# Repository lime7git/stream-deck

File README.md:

# stream-deck
 
TO DO:

- ADD RESET BUTTON                                     #CHECK
- CHANGE SWD TO GOLDPINS                               #CHECK
- ADD TWO STATUS LED DIODES                            #CHECK
- ADD FOOTPRINTS FOR MX CHERRY REPLACEMENT SWITCHES    #CHECK
- ADD TEST POINTS                                      #CHECK

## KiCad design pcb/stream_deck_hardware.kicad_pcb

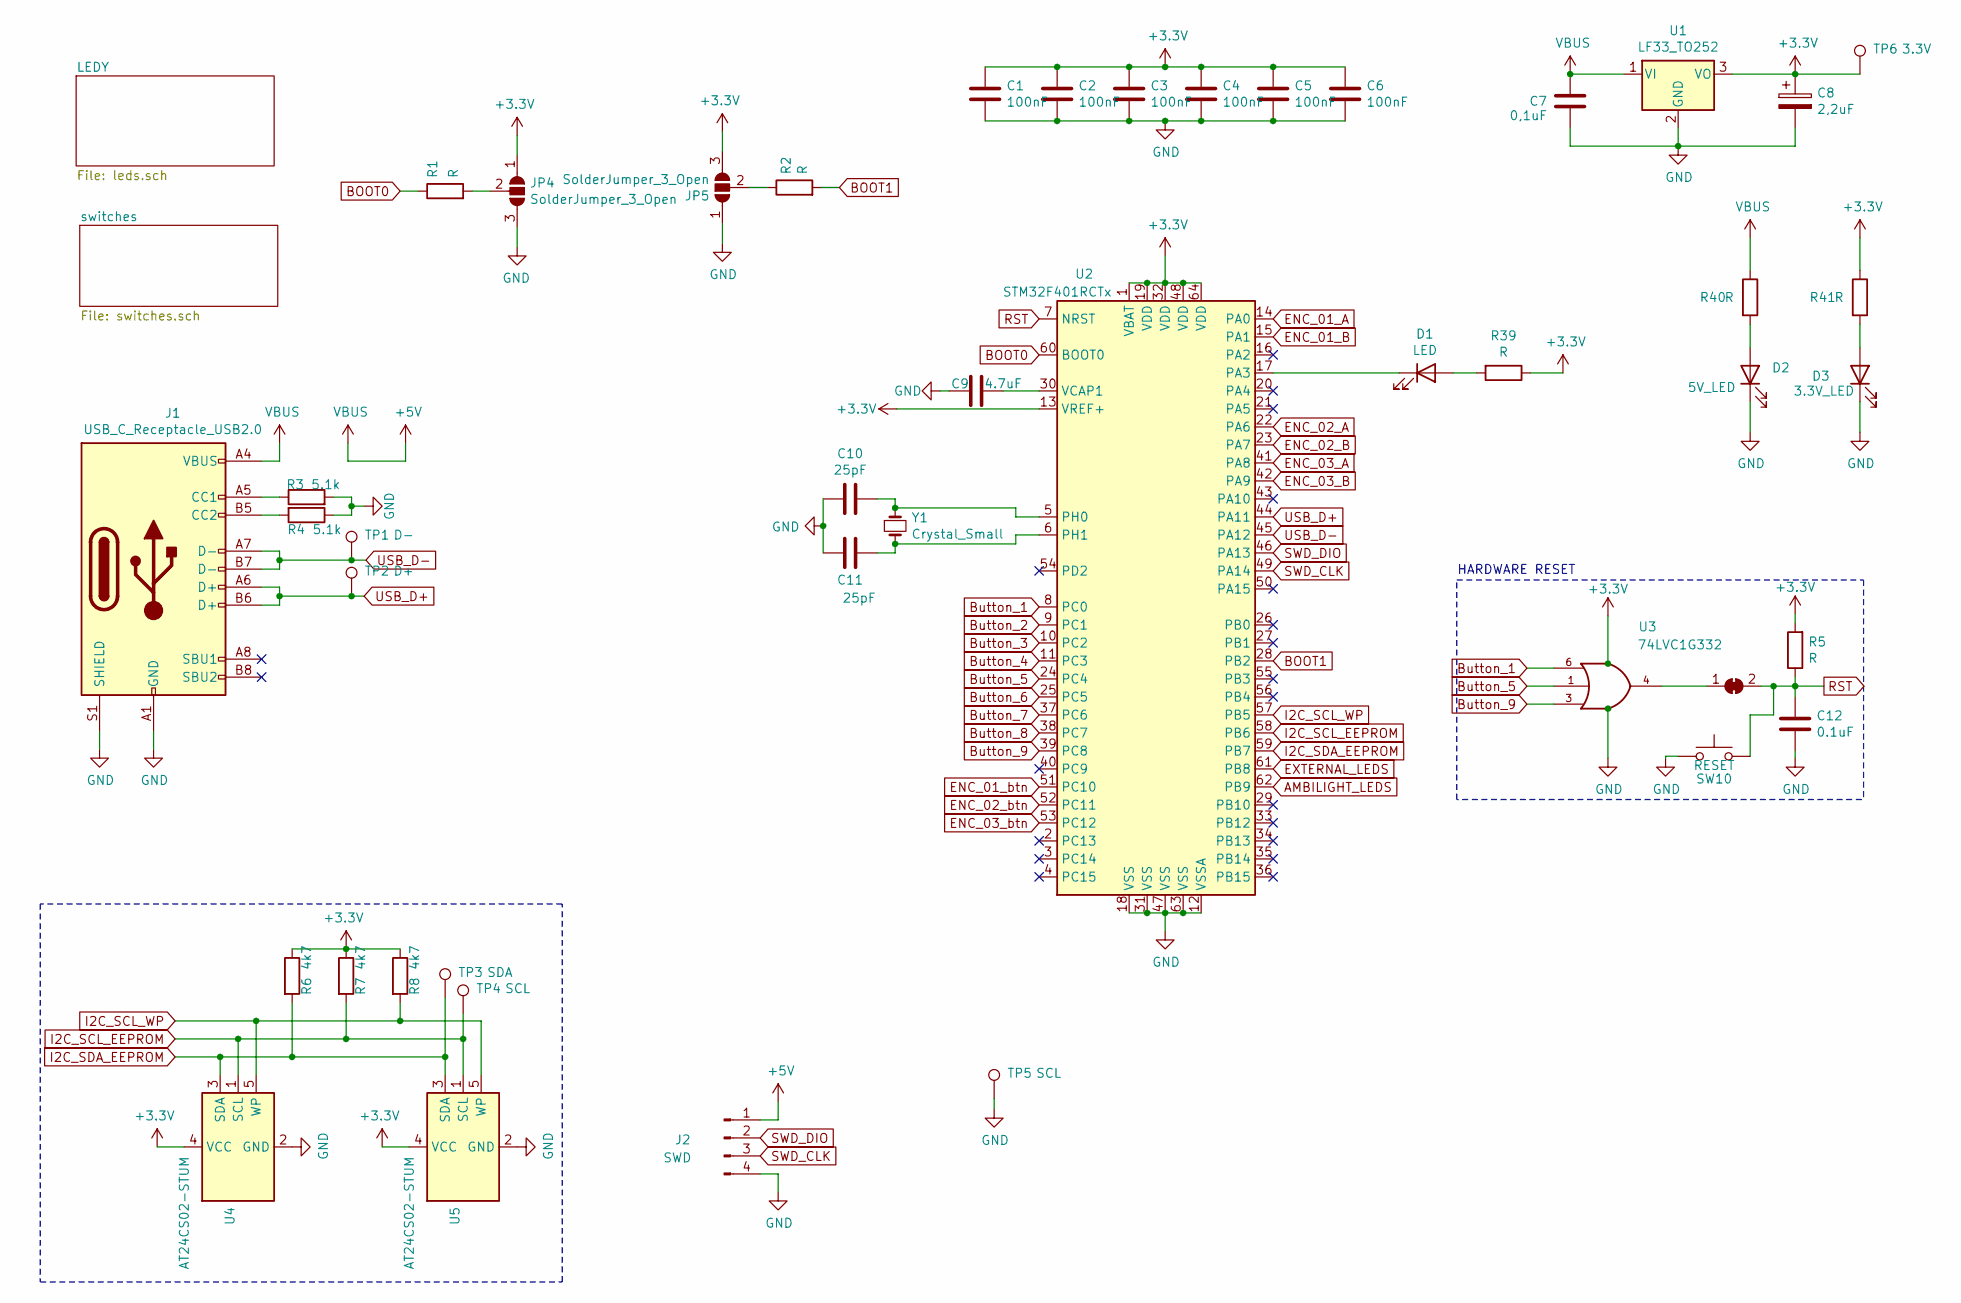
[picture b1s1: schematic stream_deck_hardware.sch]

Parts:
C1, C2, C3, C4, C5, C6: 100nF; C_0603_1608Metric
C7: 0,1uF; C_0603_1608Metric
C8: 2,2uF; C_0603_1608Metric
C9: 4.7uF; C_0603_1608Metric
C10, C11: 25pF; C_0603_1608Metric
C12: 0.1uF; C_0603_1608Metric
D1: LED; LED_0805_2012Metric
D2: 5V_LED; LED_0805_2012Metric
D3: 3.3V_LED; LED_0805_2012Metric
J1: USB_C_Receptacle_USB2.0; USB_C_Receptacle_Palconn_UTC16-G
J2: SWD; PinHeader_1x04_P2.54mm_Vertical
JP3: SolderJumper_2_Bridged; SolderJumper-2_P1.3mm_Bridged2Bar_RoundedPad1.0x1.5mm
JP4, JP5: SolderJumper_3_Open; SolderJumper-3_P1.3mm_Open_RoundedPad1.0x1.5mm
R1, R2, R5, R39, R40, R41: R; R_0603_1608Metric
R3, R4: 5.1k; R_0603_1608Metric
R6, R7, R8: 4k7; R_0603_1608Metric
SW10: RESET; SW_PUSH_6mm
TP1: D-; TestPoint_Pad_D2.0mm
TP2: D+; TestPoint_Pad_D2.0mm
TP3: SDA; TestPoint_Pad_D2.0mm
TP4, TP5: SCL; TestPoint_Pad_D2.0mm
TP6: 3.3V; TestPoint_Pad_D2.0mm
U1: LF33_TO252; TO-252-2
U2: STM32F401RCTx; LQFP-64_10x10mm_P0.5mm
U3: 74LVC1G332; SOT-23-6
U4, U5: AT24CS02-STUM; SOT-23-5
Y1: Crystal_Small; Crystal_HC49-U_Vertical

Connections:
+3V3: C1.1, C2.1, C3.1, C4.1, C5.1, C6.1, C8.1, JP4.1 (A), JP5.3 (B), R5.2, R6.1, R7.1, R8.1, R39.1, R41.1, TP6.1, U1.3 (VO), U2.1 (VBAT), U2.13 (VREF+), U2.19 (VDD), U2.32 (VDD), U2.48 (VDD), U2.64 (VDD), U3.5 (VCC), U4.4 (VCC), U5.4 (VCC); also elsewhere on the board
+5V: C7.1, J1.A4 (VBUS), J1.A9 (VBUS), J1.B4 (VBUS), J1.B9 (VBUS), J2.1, R40.1, U1.1 (VI); also elsewhere on the board
AMBILIGHT_LEDS: U2.62 (PB9); also elsewhere on the board
BOOT0: R1.1, U2.60 (BOOT0)
BOOT1: R2.2, U2.28 (PB2)
Button_1: U2.8 (PC0), U3.6; also elsewhere on the board
Button_2: U2.9 (PC1); also elsewhere on the board
Button_3: U2.10 (PC2); also elsewhere on the board
Button_4: U2.11 (PC3); also elsewhere on the board
Button_5: U2.24 (PC4), U3.1; also elsewhere on the board
Button_6: U2.25 (PC5); also elsewhere on the board
Button_7: U2.37 (PC6); also elsewhere on the board
Button_8: U2.38 (PC7); also elsewhere on the board
Button_9: U2.39 (PC8), U3.3; also elsewhere on the board
ENC_01_A: U2.14 (PA0); also elsewhere on the board
ENC_01_B: U2.15 (PA1); also elsewhere on the board
ENC_01_btn: U2.51 (PC10); also elsewhere on the board
ENC_02_A: U2.22 (PA6); also elsewhere on the board
ENC_02_B: U2.23 (PA7); also elsewhere on the board
ENC_02_btn: U2.52 (PC11); also elsewhere on the board
ENC_03_A: U2.41 (PA8); also elsewhere on the board
ENC_03_B: U2.42 (PA9); also elsewhere on the board
ENC_03_btn: U2.53 (PC12); also elsewhere on the board
EXTERNAL_LEDS: U2.61 (PB8); also elsewhere on the board
GND: C1.2, C2.2, C3.2, C4.2, C5.2, C6.2, C7.2, C8.2, C9.1, C10.2, C11.2, C12.2, D2.1 (K), D3.1 (K), J1.A1 (GND), J1.A12 (GND), J1.B1 (GND), J1.B12 (GND), J1.S1 (SHIELD), J2.4, JP4.3 (B), JP5.1 (A), R3.2, R4.1, SW10.1, TP5.1, U1.2 (GND), U2.12 (VSSA), U2.18 (VSS), U2.31 (VSS), U2.47 (VSS), U2.63 (VSS), U3.2 (GND), U4.2 (GND), U5.2 (GND); also elsewhere on the board
I2C_SCL_EEPROM: R7.2, TP4.1, U2.58 (PB6), U4.1 (SCL), U5.1 (SCL)
I2C_SCL_WP: R8.2, U2.57 (PB5), U4.5 (WP), U5.5 (WP)
I2C_SDA_EEPROM: R6.2, TP3.1, U2.59 (PB7), U4.3 (SDA), U5.3 (SDA)
unnamed: C9.2, U2.30 (VCAP1)
unnamed: C10.1, U2.5 (PH0), Y1.1
unnamed: C11.1, U2.6 (PH1), Y1.2
unnamed: D1.1 (K), U2.17 (PA3)
unnamed: D1.2 (A), R39.2
unnamed: D2.2 (A), R40.2
unnamed: D3.2 (A), R41.2
unnamed: J1.A5 (CC1), R3.1
unnamed: J1.B5 (CC2), R4.2
unnamed: JP3.1 (A), U3.4
unnamed: JP4.2 (C), R1.2
unnamed: JP5.2 (C), R2.1
RST: C12.1, JP3.2 (B), R5.1, SW10.2, U2.7 (NRST); also elsewhere on the board
SWD_CLK: J2.3, U2.49 (PA14); also elsewhere on the board
SWD_DIO: J2.2, U2.46 (PA13); also elsewhere on the board
USB_D+: J1.A6 (D+), J1.B6 (D+), TP2.1, U2.44 (PA11); also elsewhere on the board
USB_D-: J1.A7 (D-), J1.B7 (D-), TP1.1, U2.45 (PA12); also elsewhere on the board

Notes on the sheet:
HARDWARE RESET

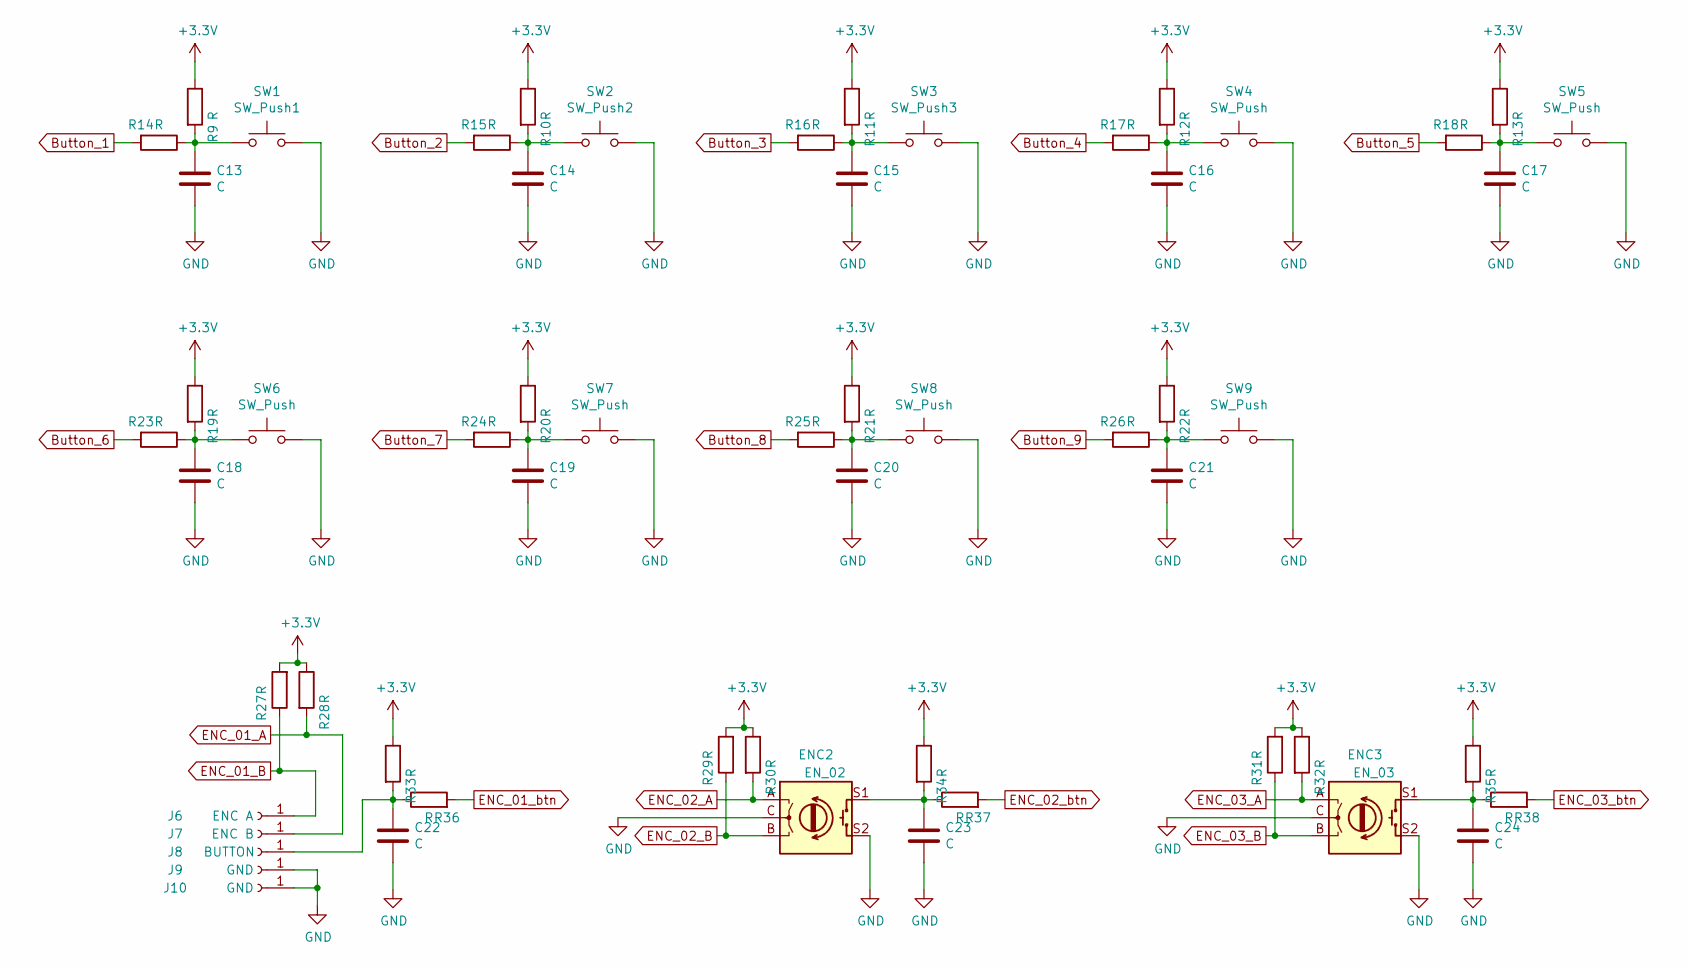
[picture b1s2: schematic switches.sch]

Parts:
C13, C14, C15, C16, C17, C18, C19, C20, C21, C22, C23, C24: C; C_0603_1608Metric
ENC2: EN_02; RotaryEncoder_Alps_EC11E-Switch_Vertical_H20mm_CircularMoun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
ENC3: EN_03; RotaryEncoder_Alps_EC11E-Switch_Vertical_H20mm_CircularMoun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
J6: ENC A; TestPoint_Pad_D2.0mm
J7: ENC B; TestPoint_Pad_D2.0mm
J8: BUTTON; TestPoint_Pad_D2.0mm
J9, J10: GND; TestPoint_Pad_D2.0mm
R9, R10, R11, R12, R13, R14, R15, R16, R17, R18, R19, R20, R21, R22, R23, R24, R25, R26, R27, R28, R29, R30, R31, R32, R33, R34, R35, R36, R37, R38: R; R_0603_1608Metric
SW1: SW_Push1; SW_Cherry_MX_1.00u_PCB
SW2: SW_Push2; SW_Cherry_MX_1.00u_PCB
SW3: SW_Push3; SW_Cherry_MX_1.00u_PCB
SW4, SW5, SW6, SW7, SW8, SW9: SW_Push; SW_Cherry_MX_1.00u_PCB

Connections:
+3V3: R9.1, R10.1, R11.1, R12.1, R13.1, R19.1, R20.1, R21.1, R22.1, R27.2, R28.1, R29.2, R30.1, R31.2, R32.1, R33.1, R34.1, R35.1; also elsewhere on the board
Button_1: R14.2; also elsewhere on the board
Button_2: R15.2; also elsewhere on the board
Button_3: R16.2; also elsewhere on the board
Button_4: R17.2; also elsewhere on the board
Button_5: R18.2; also elsewhere on the board
Button_6: R23.2; also elsewhere on the board
Button_7: R24.2; also elsewhere on the board
Button_8: R25.2; also elsewhere on the board
Button_9: R26.2; also elsewhere on the board
ENC_01_A: J7.1, R28.2; also elsewhere on the board
ENC_01_B: J6.1, R27.1; also elsewhere on the board
ENC_01_btn: R36.2; also elsewhere on the board
ENC_02_A: ENC2.A, R30.2; also elsewhere on the board
ENC_02_B: ENC2.B, R29.1; also elsewhere on the board
ENC_02_btn: R37.2; also elsewhere on the board
ENC_03_A: ENC3.A, R32.2; also elsewhere on the board
ENC_03_B: ENC3.B, R31.1; also elsewhere on the board
ENC_03_btn: R38.2; also elsewhere on the board
GND: C13.2, C14.2, C15.2, C16.2, C17.2, C18.2, C19.2, C20.2, C21.2, C22.2, C23.2, C24.2, ENC2.C, ENC2.S2, ENC3.C, ENC3.S2, J9.1, J10.1, SW1.2, SW2.2, SW3.2, SW4.2, SW5.2, SW6.2, SW7.2, SW8.2, SW9.2; also elsewhere on the board
unnamed: C13.1, R9.2, R14.1, SW1.1
unnamed: C14.1, R10.2, R15.1, SW2.1
unnamed: C15.1, R11.2, R16.1, SW3.1
unnamed: C16.1, R12.2, R17.1, SW4.1
unnamed: C17.1, R13.2, R18.1, SW5.1
unnamed: C18.1, R19.2, R23.1, SW6.1
unnamed: C19.1, R20.2, R24.1, SW7.1
unnamed: C20.1, R21.2, R25.1, SW8.1
unnamed: C21.1, R22.2, R26.1, SW9.1
unnamed: C22.1, J8.1, R33.2, R36.1
unnamed: C23.1, ENC2.S1, R34.2, R37.1
unnamed: C24.1, ENC3.S1, R35.2, R38.1

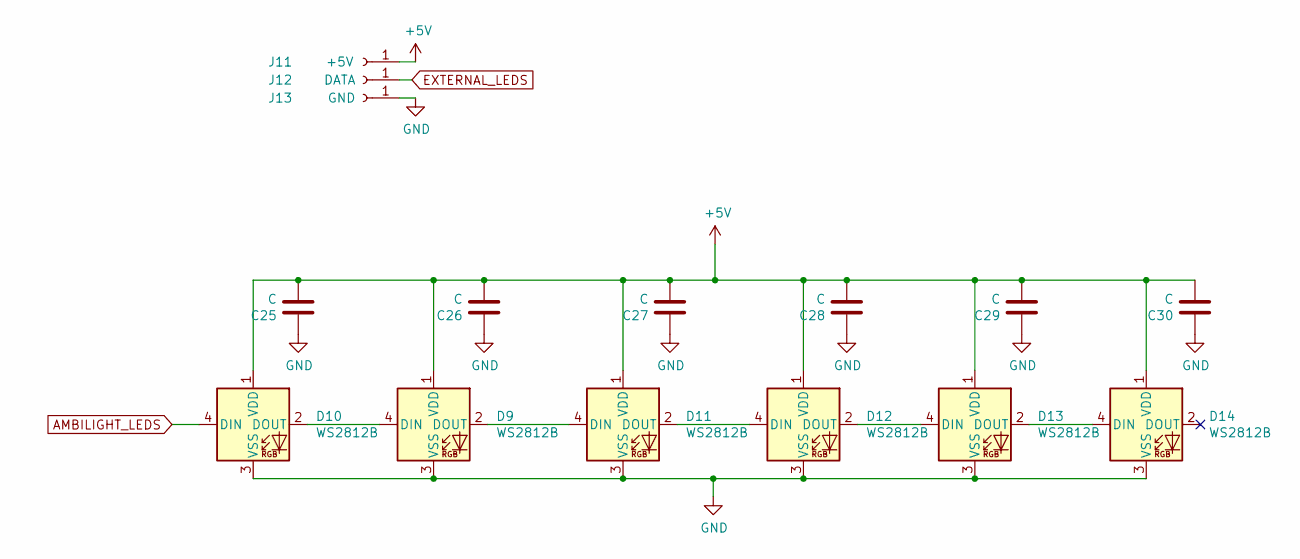
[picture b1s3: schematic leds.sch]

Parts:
C25, C26, C27, C28, C29, C30: C; C_0603_1608Metric
D9, D10, D11, D12, D13, D14: WS2812B; LED_WS2812B_PLCC4_5.0x5.0mm_P3.2mm
J11: +5V; TestPoint_Pad_D2.0mm
J12: DATA; TestPoint_Pad_D2.0mm
J13: GND; TestPoint_Pad_D2.0mm

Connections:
+5V: C25.2, C26.2, C27.2, C28.2, C29.2, C30.2, D9.1 (VDD), D10.1 (VDD), D11.1 (VDD), D12.1 (VDD), D13.1 (VDD), D14.1 (VDD), J11.1; also elsewhere on the board
AMBILIGHT_LEDS: D10.4 (DIN); also elsewhere on the board
EXTERNAL_LEDS: J12.1; also elsewhere on the board
GND: C25.1, C26.1, C27.1, C28.1, C29.1, C30.1, D9.3 (VSS), D10.3 (VSS), D11.3 (VSS), D12.3 (VSS), D13.3 (VSS), D14.3 (VSS), J13.1; also elsewhere on the board
unnamed: D9.4 (DIN), D10.2 (DOUT)
unnamed: D11.2 (DOUT), D12.4 (DIN)
unnamed: D9.2 (DOUT), D11.4 (DIN)
unnamed: D12.2 (DOUT), D13.4 (DIN)
unnamed: D13.2 (DOUT), D14.4 (DIN)

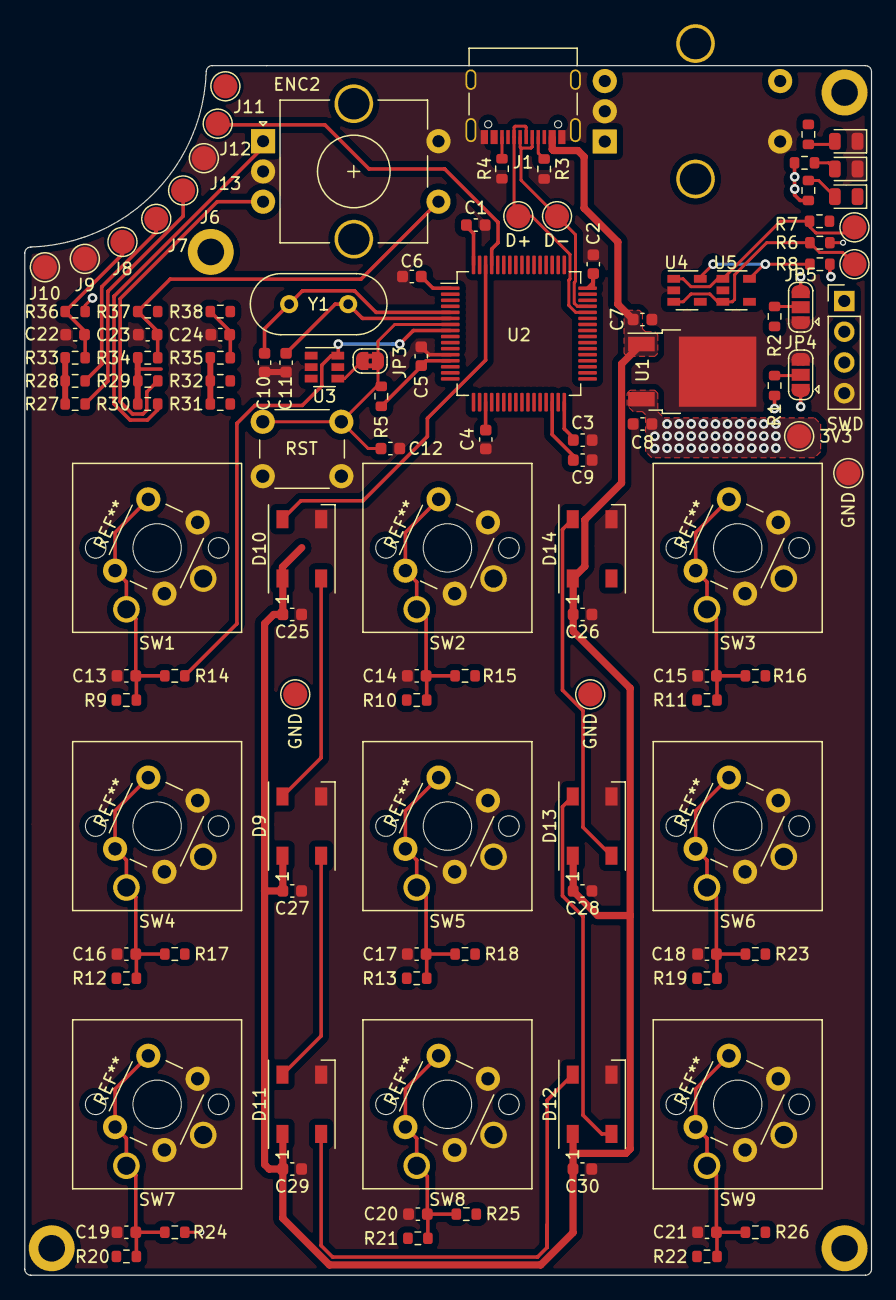
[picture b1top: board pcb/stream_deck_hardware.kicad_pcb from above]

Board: 4 copper layers, 70.0 x 100.0 mm, 119 parts (1 on the bottom side), 62 nets.

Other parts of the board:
3V3: 3.3V; TestPoint_Pad_D2.0mm
D+: D+; TestPoint_Pad_D2.0mm
D-: D-; TestPoint_Pad_D2.0mm
GND: SCL; TestPoint_Pad_D2.0mm
GND#2, GND#3: SCL; TestPoint_Pad_D2.0mm
RST: RESET; SW_PUSH_6mm
SWD: SWD; PinHeader_1x04_P2.54mm_Vertical

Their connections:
+3V3: 3V3.1; also elsewhere on the board
+5V: SWD.1; also elsewhere on the board
GND: GND#3.1, RST.1, SWD.4; also elsewhere on the board
RST: RST.2; also elsewhere on the board
SWD_CLK: SWD.3; also elsewhere on the board
SWD_DIO: SWD.2; also elsewhere on the board
USB_D+: D+.1; also elsewhere on the board
USB_D-: D-.1; also elsewhere on the board

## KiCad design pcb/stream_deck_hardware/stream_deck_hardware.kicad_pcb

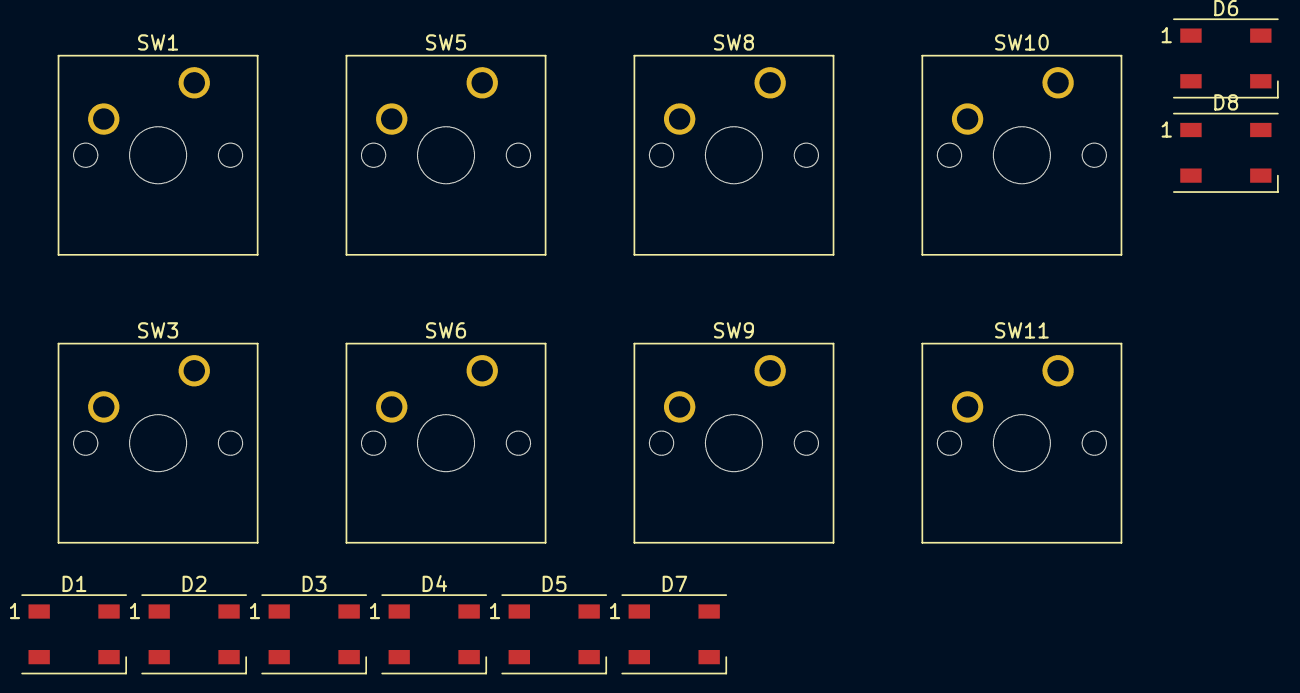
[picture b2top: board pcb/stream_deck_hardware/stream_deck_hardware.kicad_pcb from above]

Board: 2 copper layers, 16 parts (0 on the bottom side), 9 nets, no tracks yet.

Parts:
D1, D2, D3, D4, D5, D6, D7, D8: WS2812B; LED_WS2812B_PLCC4_5.0x5.0mm_P3.2mm
SW1, SW3, SW5, SW6, SW8, SW9, SW10, SW11: SW_Push_LED; SW_Cherry_MX_1.00u_PCB

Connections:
+5V: D1.1, D2.1, D3.1, D4.1, D5.1, D6.1, D7.1, D8.1
GND: D1.3, D2.3, D3.3, D4.3, D5.3, D6.3, D7.3, D8.3
unnamed: D1.2, D2.4
unnamed: D2.2, D3.4
unnamed: D3.2, D4.4
unnamed: D4.2, D5.4
unnamed: D5.2, D6.4
unnamed: D6.2, D7.4
unnamed: D7.2, D8.4

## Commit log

2021-11-08 Added excel sheet with needed parts
2021-11-08 case
    First sugestion of stream-deck case
2021-11-08 Added encoder cad model and excel sheet with needed parts
2021-11-08 Change encoder
2021-11-08 First concept of electronic case
    assembly in SOLIDWORKS
2021-11-08 Excel update
2021-11-08 Added gitignore for software test
2021-11-15 Kicad designing PCB
    Kicad
2021-11-15 electrical schematic desiging
2021-11-15 Added some datesheets
2021-11-15 Clean up
2021-11-16 Added some documentations
2021-11-17 Schematic upgrade
2021-11-17 Added boot pins jumper selector
2021-11-17 Added STM32 boot modes application note AN2606
2021-11-18 Schematic update
2021-11-18 Schematic version 1.0
2021-11-18 Added EEPROM memory & some footprints
2022-01-13 Finish schematic and added footprints
2022-01-13 Footprints update and some changes
2022-01-13 PCB edges prototype
2022-01-15 Components positioning
2022-01-15 Components placement
2022-01-16 Components placement, added 3d model of cherry mx switch
2022-01-16 Remove usb wire connector
2022-01-16 Added encoder, and usb-c 3d models
2022-01-16 Component placement
2022-01-18 Change connectors footprints
2022-01-18 Pads placement
2022-01-19 Bugfix
2022-01-19 Component placement version 1.0
2022-02-13 Ibom
2022-03-30 puszuje to
